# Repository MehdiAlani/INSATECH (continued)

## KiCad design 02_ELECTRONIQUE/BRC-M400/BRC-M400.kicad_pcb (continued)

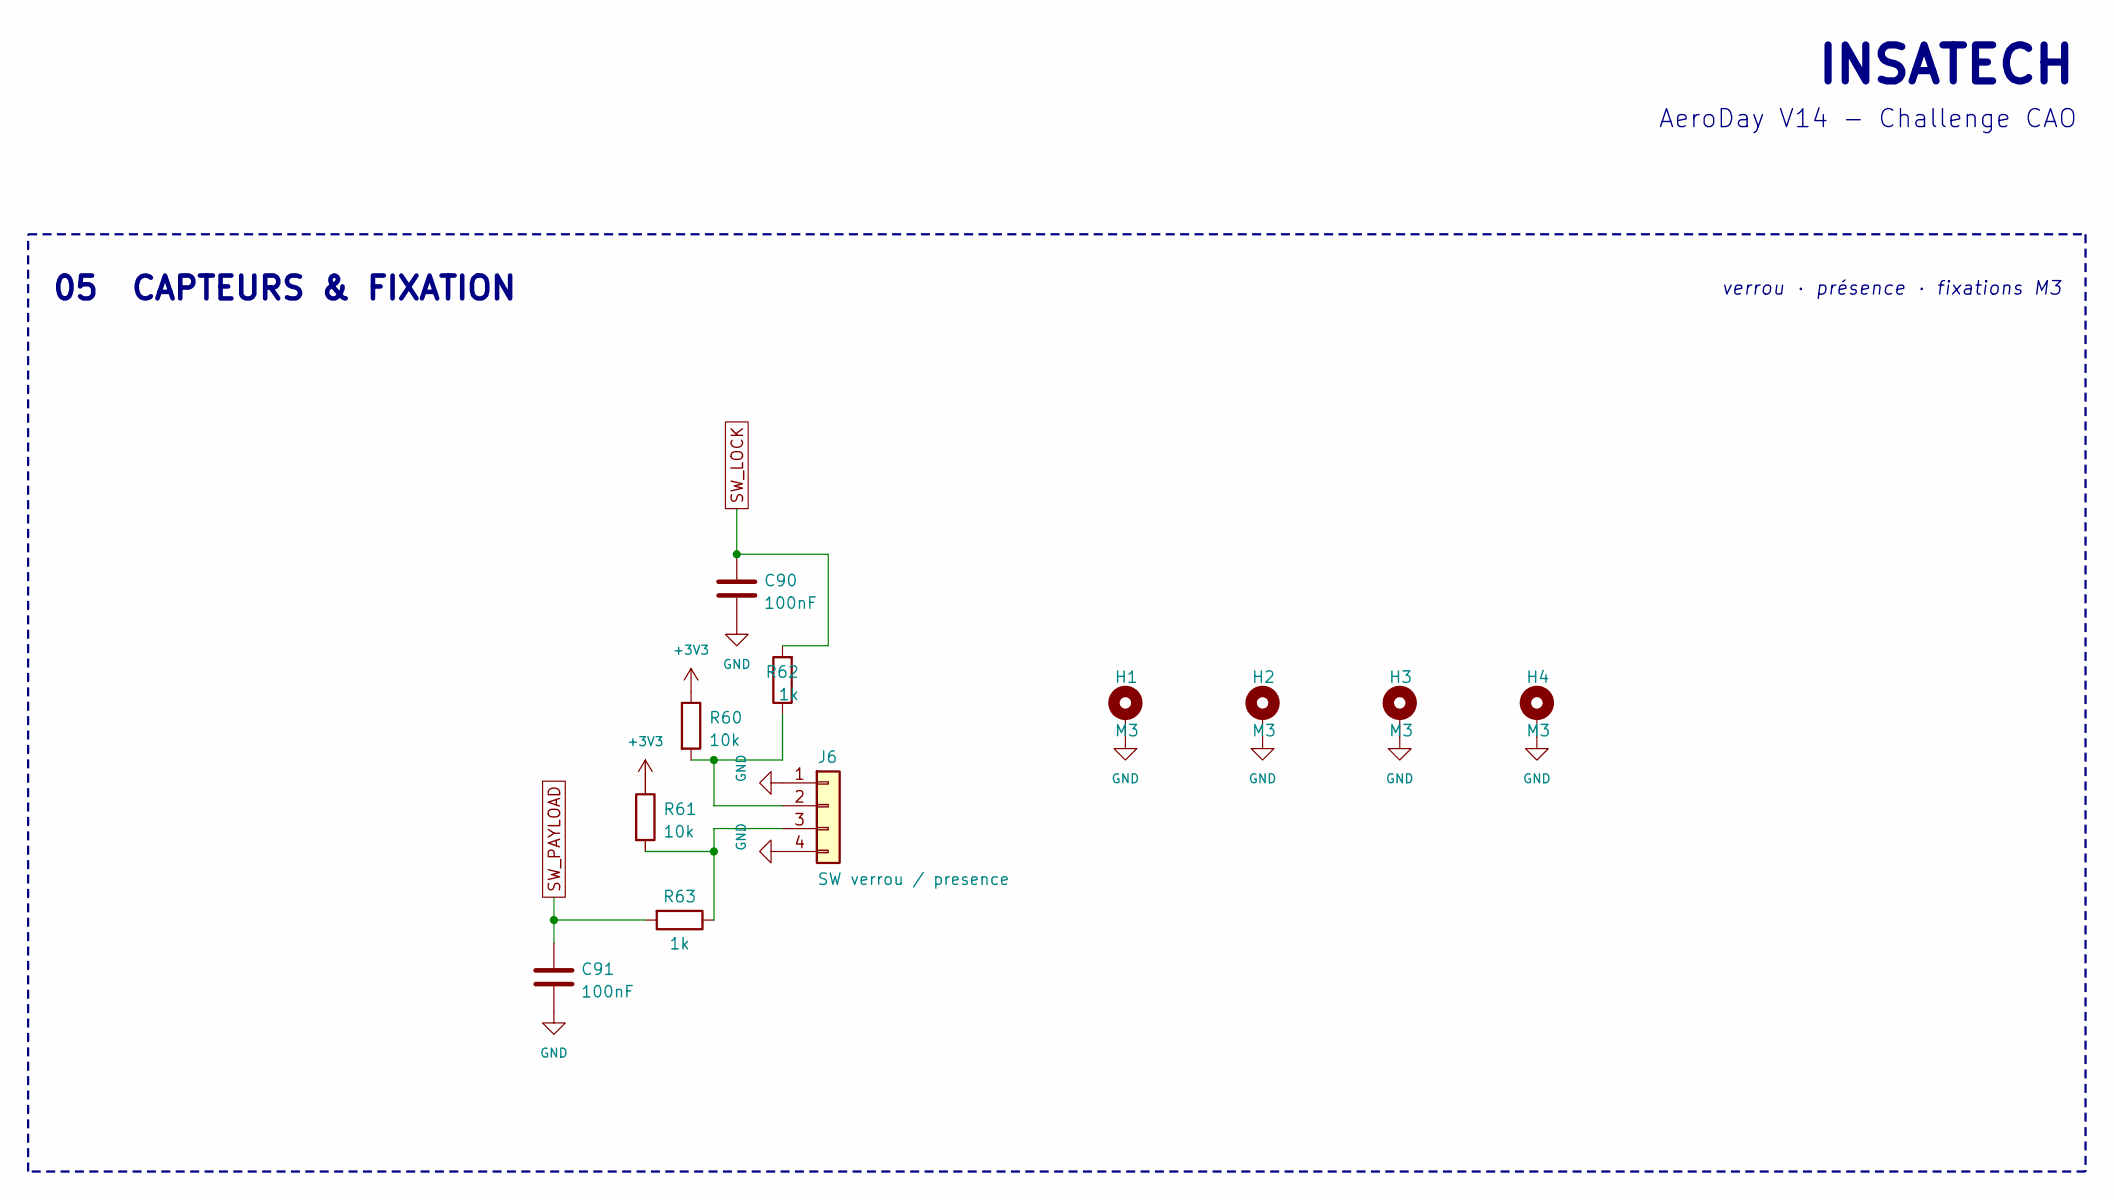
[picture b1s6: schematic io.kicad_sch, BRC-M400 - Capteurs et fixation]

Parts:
C90, C91: 100nF; C_0603_1608Metric
H1, H2, H3, H4: M3; MountingHole_3.2mm_M3_Pad_Via
J6: SW verrou / presence; JST_GH_SM04B-GHS-TB_1x04-1MP_P1.25mm_Horizontal; MPN SM04B-GHS-TB
R60, R61: 10k; R_0603_1608Metric
R62, R63: 1k; R_0603_1608Metric

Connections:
unnamed: J6.2, R60.2, R62.1
unnamed: J6.3, R61.2, R63.1
SW_LOCK: C90.1, R62.2; also elsewhere on the board
SW_PAYLOAD: C91.1, R63.2; also elsewhere on the board

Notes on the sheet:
INSATECH
AeroDay V14 - Challenge CAO
05 CAPTEURS & FIXATION
verrou · présence · fixations M3

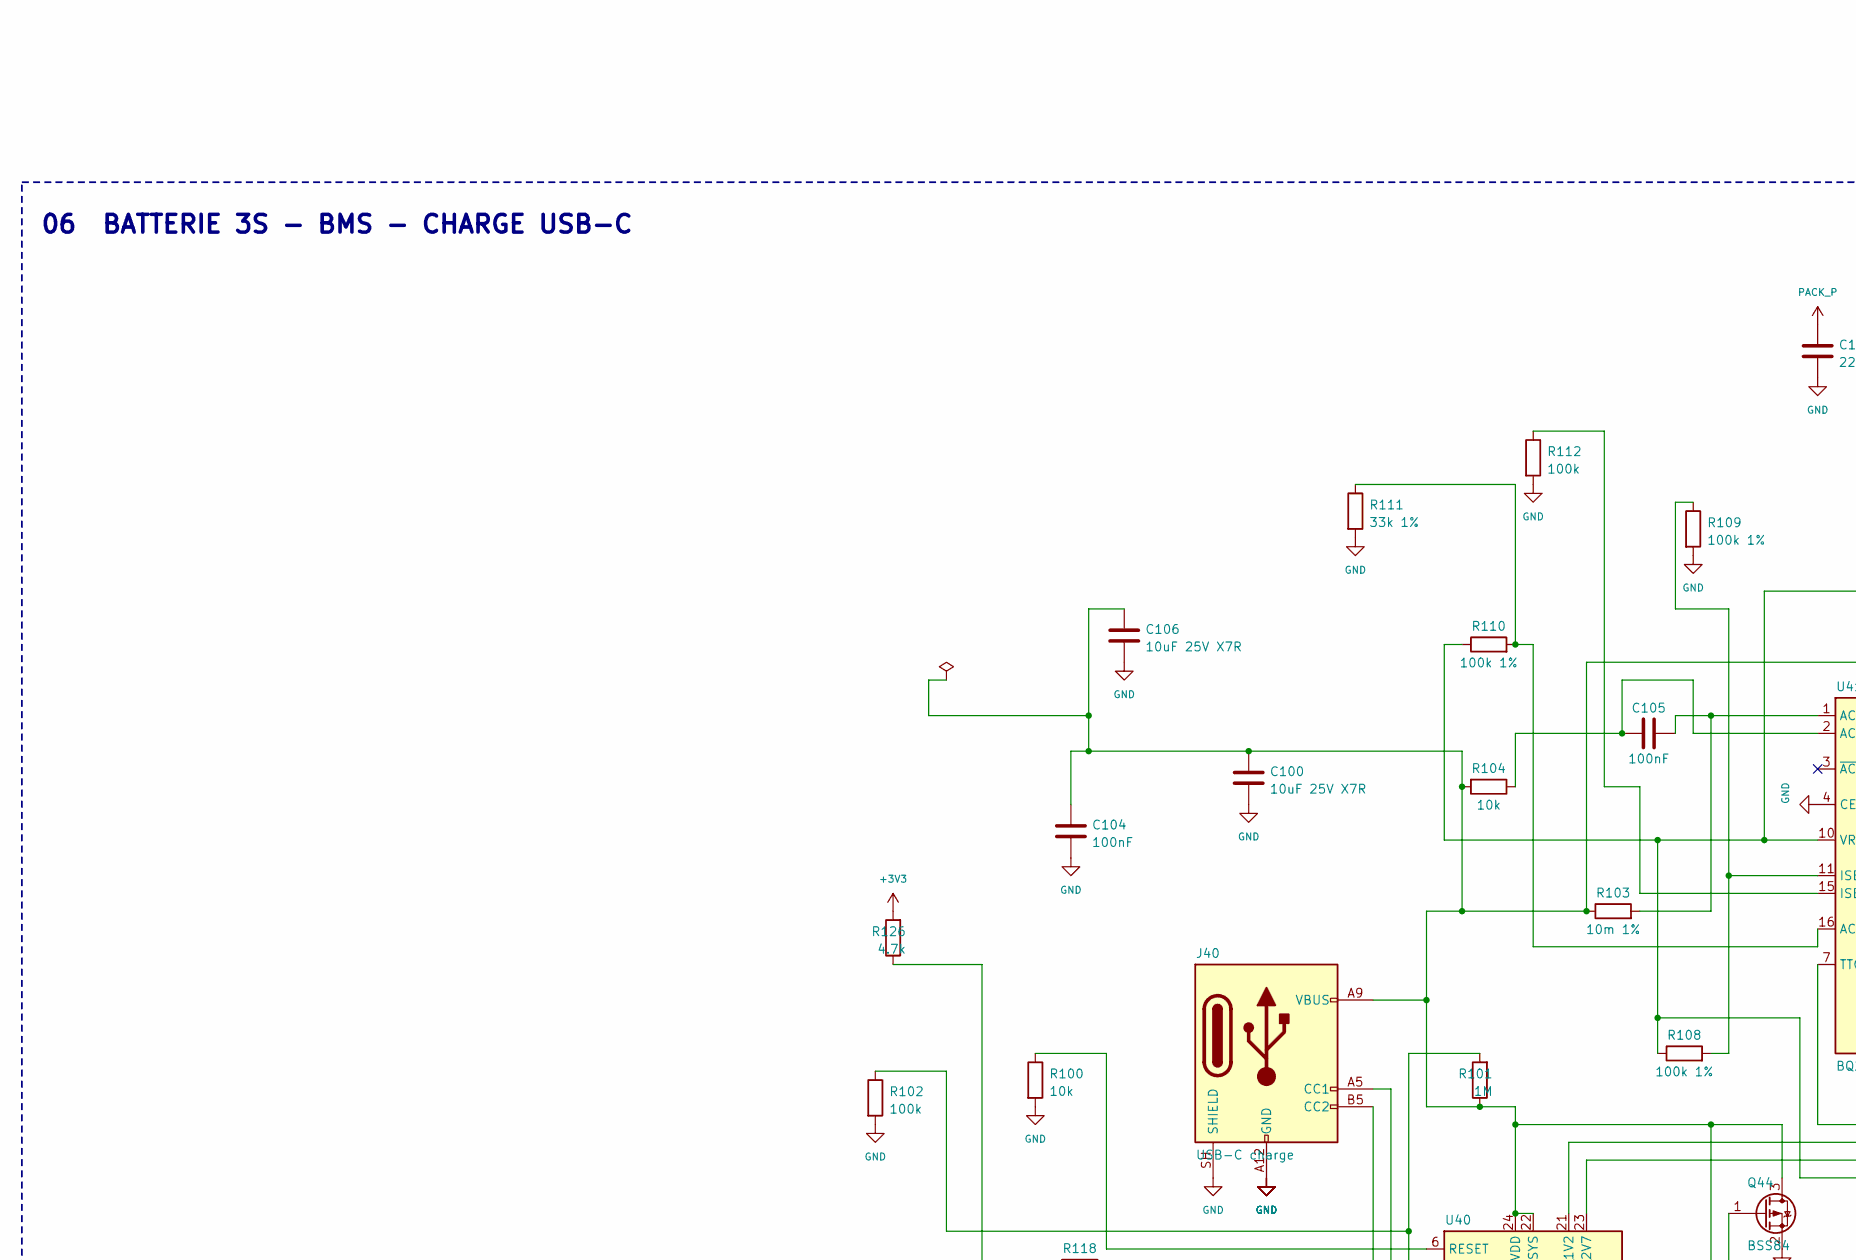
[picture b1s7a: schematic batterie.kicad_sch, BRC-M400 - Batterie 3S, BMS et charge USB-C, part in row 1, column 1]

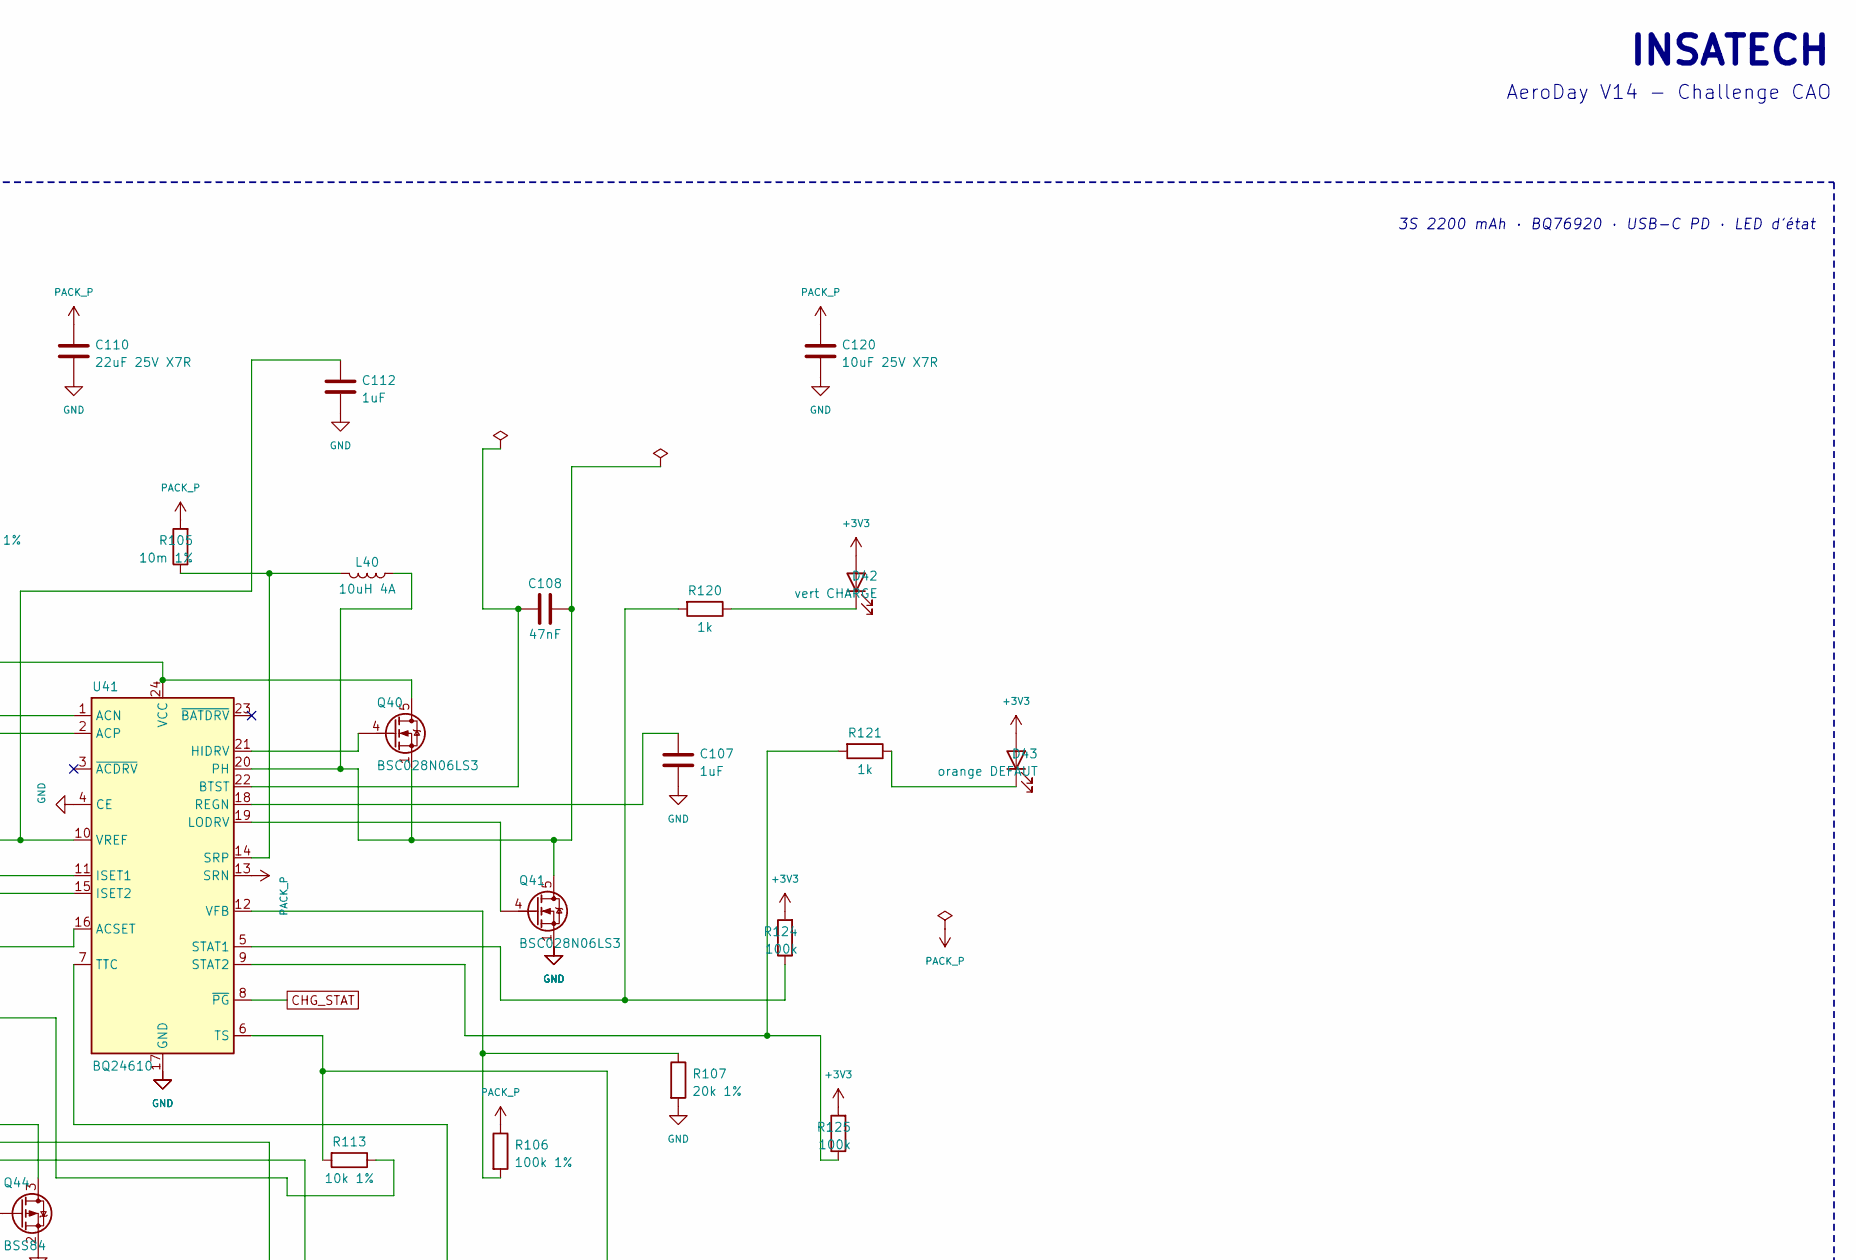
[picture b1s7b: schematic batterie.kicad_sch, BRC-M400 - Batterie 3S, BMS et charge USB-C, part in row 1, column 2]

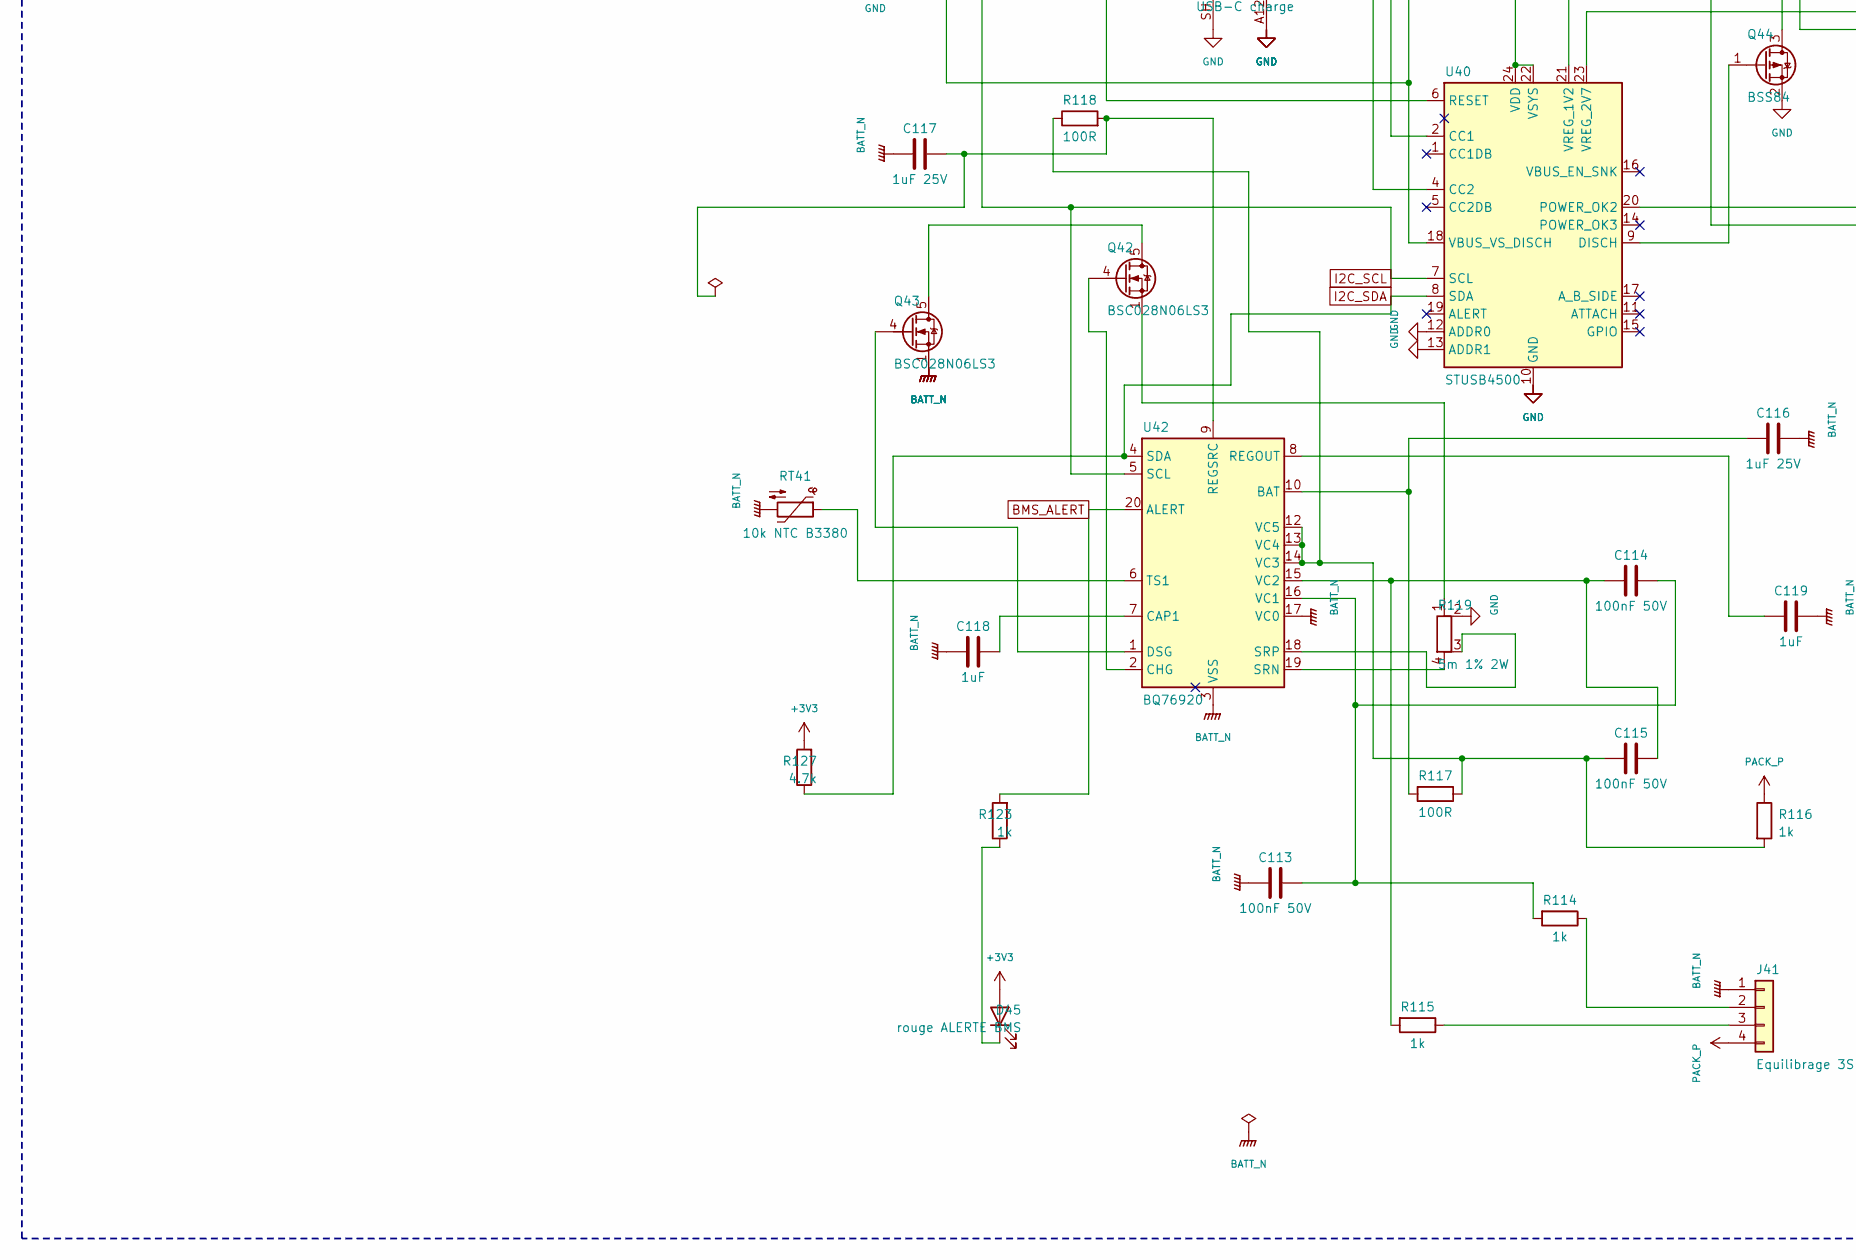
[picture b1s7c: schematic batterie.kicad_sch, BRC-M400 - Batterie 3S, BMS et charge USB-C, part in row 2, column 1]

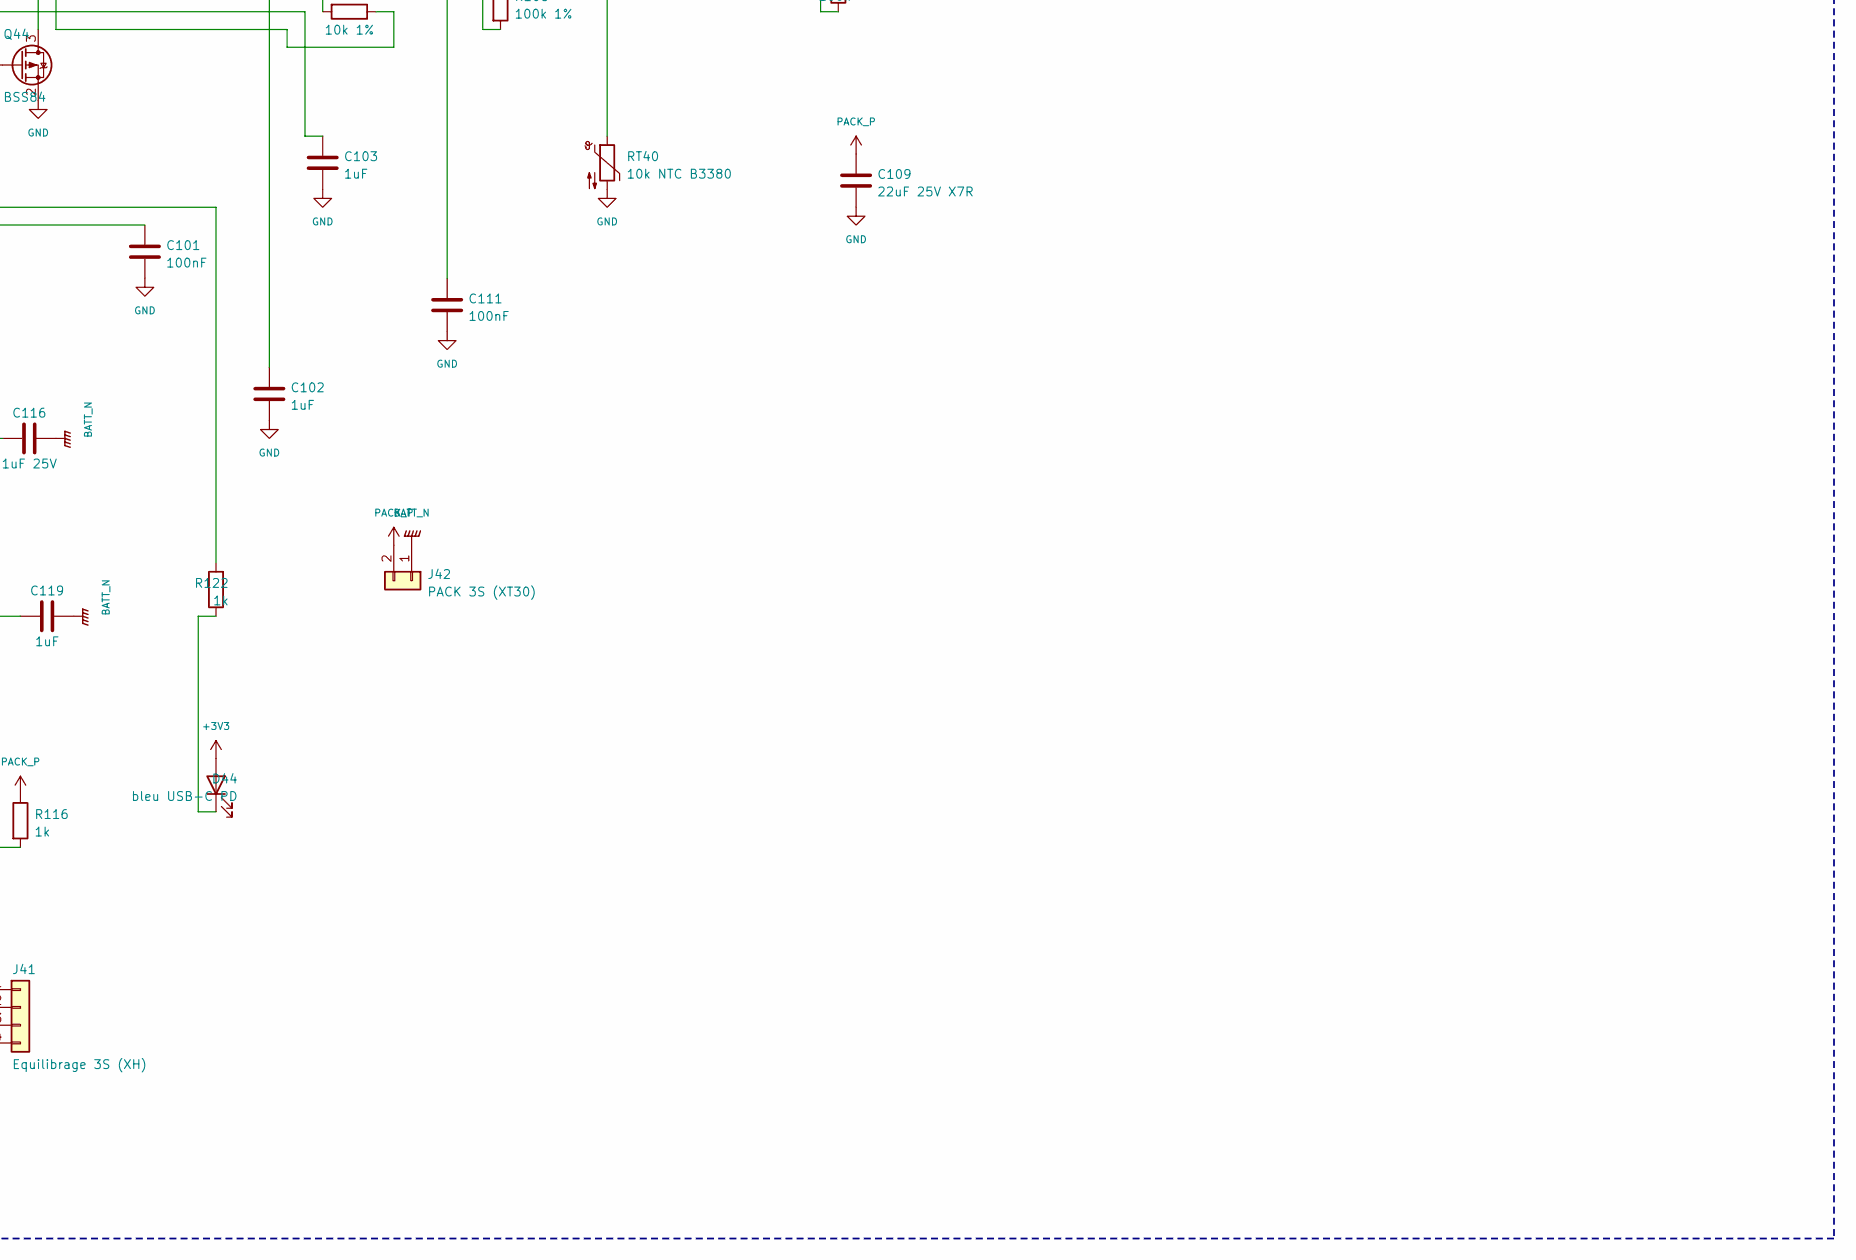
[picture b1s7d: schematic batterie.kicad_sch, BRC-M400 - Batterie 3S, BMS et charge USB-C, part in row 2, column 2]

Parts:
C100, C106, C120: 10uF 25V X7R; C_1210_3225Metric
C101: 100nF; C_0603_1608Metric
C102, C103, C112, C118, C119: 1uF; C_0402_1005Metric
C104, C105, C111: 100nF; C_0402_1005Metric
C107: 1uF; C_0603_1608Metric
C108: 47nF; C_0402_1005Metric
C109, C110: 22uF 25V X7R; C_1210_3225Metric
C113, C114, C115: 100nF 50V; C_0603_1608Metric
C116, C117: 1uF 25V; C_0603_1608Metric
D42: vert CHARGE; LED_0805_2012Metric
D43: orange DEFAUT; LED_0805_2012Metric
D44: bleu USB-C PD; LED_0805_2012Metric
D45: rouge ALERTE BMS; LED_0805_2012Metric
J40: USB-C charge; USB_C_Receptacle_GCT_USB4085; MPN USB4085-GF-A
J41: Equilibrage 3S (XH); JST_XH_B4B-XH-A_1x04_P2.50mm_Vertical; MPN B4B-XH-A
J42: PACK 3S (XT30); AMASS_XT30PW-M_1x02_P2.50mm_Horizontal; MPN XT30PW-M
L40: 10uH 4A; L_Bourns_SRN6045TA; MPN SRN6045TA-100M
Q40, Q41, Q42, Q43: BSC028N06LS3; TDSON-8-1; MPN BSC028N06LS3GATMA1
Q44: BSS84; SOT-23
R100, R104: 10k; R_0402_1005Metric
R101: 1M; R_0402_1005Metric
R102, R124, R125: 100k; R_0402_1005Metric
R103, R105: 10m 1%; R_2512_6332Metric; MPN CSS2512
R106, R108, R109, R110: 100k 1%; R_0603_1608Metric
R107: 20k 1%; R_0603_1608Metric
R111: 33k 1%; R_0603_1608Metric
R112: 100k; R_0603_1608Metric
R113: 10k 1%; R_0603_1608Metric
R114, R115, R116: 1k; R_0603_1608Metric
R117, R118: 100R; R_0603_1608Metric
R119: 5m 1% 2W; R_2512_6332Metric; MPN WSL2512R0050FEA
R120, R121, R122, R123: 1k; R_0402_1005Metric
R126, R127: 4.7k; R_0402_1005Metric
RT40, RT41: 10k NTC B3380; R_0603_1608Metric
U40: STUSB4500; QFN-24-1EP_4x4mm_P0.5mm_EP2.8x2.8mm; MPN STUSB4500QTR
U41: BQ24610; QFN-24-1EP_4x4mm_P0.5mm_EP2.5x2.5mm; MPN BQ24610RGER
U42: BQ76920; TSSOP-20_4.4x6.5mm_P0.65mm; MPN BQ76920PWR

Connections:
BATT_N: C113.2, C116.2, C117.2, C118.2, C119.2, J41.1, J42.1, Q43.1 (S), Q43.2 (S), Q43.3 (S), RT41.2, U42.3 (VSS), U42.17 (VC0)
BMS_ALERT: R123.2, U42.20 (ALERT); also elsewhere on the board
CHG_STAT: U41.8 (~PG); also elsewhere on the board
I2C_SCL: R126.1, U40.7 (SCL), U42.5 (SCL); also elsewhere on the board
I2C_SDA: R127.1, U40.8 (SDA), U42.4 (SDA); also elsewhere on the board
unnamed: D42.1 (K), R120.1
unnamed: D43.1 (K), R121.1
unnamed: D44.1 (K), R122.1
unnamed: D45.1 (K), R123.1
unnamed: J40.A5 (CC1), U40.2 (CC1)
unnamed: J40.B5 (CC2), U40.4 (CC2)
unnamed: J41.2, R114.1
unnamed: J41.3, R115.1
unnamed: C100.1, C101.1, C104.1, C106.1, J40.A4 (VBUS), J40.A9 (VBUS), J40.B4 (VBUS), J40.B9 (VBUS), Q40.5 (D), Q44.3 (D), R101.1, R103.1, R104.2, U40.22 (VSYS), U40.24 (VDD), U41.24 (VCC)
unnamed: Q40.4 (G), U41.21 (HIDRV)
unnamed: C108.2, L40.1, Q40.1 (S), Q40.2 (S), Q40.3 (S), Q41.5 (D), U41.20 (PH)
unnamed: Q41.4 (G), U41.19 (LODRV)
unnamed: Q42.5 (D), Q43.5 (D)
unnamed: Q42.4 (G), U42.2 (CHG)
unnamed: Q42.1 (S), Q42.2 (S), Q42.3 (S), R119.1
unnamed: Q43.4 (G), U42.1 (DSG)
unnamed: Q44.1 (G), U40.9 (DISCH)
unnamed: R122.2, U40.20 (POWER_OK2)
unnamed: R100.1, U40.6 (RESET)
unnamed: R101.2, R102.1, U40.18 (VBUS_VS_DISCH)
unnamed: C102.1, U40.21 (VREG_1V2)
unnamed: C103.1, U40.23 (VREG_2V7)
unnamed: C105.1, R103.2, U41.1 (ACN)
unnamed: C105.2, R104.1, U41.2 (ACP)
unnamed: R110.2, R111.1, U41.16 (ACSET)
unnamed: C108.1, U41.22 (BTST)
unnamed: R108.2, R109.1, U41.11 (ISET1)
unnamed: R112.1, U41.15 (ISET2)
unnamed: C107.1, U41.18 (REGN)
unnamed: L40.2, R105.1, U41.14 (SRP)
unnamed: R120.2, R124.1, U41.5 (STAT1)
unnamed: R121.2, R125.1, U41.9 (STAT2)
unnamed: R113.2, RT40.1, U41.6 (TS)
unnamed: C111.1, U41.7 (TTC)
unnamed: R106.2, R107.1, U41.12 (VFB)
unnamed: C112.1, R108.1, R110.1, R113.1, U41.10 (VREF)
unnamed: C116.1, R117.2, U42.10 (BAT)
unnamed: C118.1, U42.7 (CAP1)
unnamed: C119.1, U42.8 (REGOUT)
unnamed: C117.1, R118.2, U42.9 (REGSRC)
unnamed: R119.4, U42.19 (SRN)
unnamed: R119.3, U42.18 (SRP)
unnamed: RT41.1, U42.6 (TS1)
unnamed: C113.1, C114.2, R114.2, U42.16 (VC1)
unnamed: C114.1, C115.2, R115.2, U42.15 (VC2)
unnamed: C115.1, R116.2, R117.1, R118.1, U42.12 (VC5), U42.13 (VC4), U42.14 (VC3)
PACK_P: C109.1, C110.1, C120.1, J41.4, J42.2, R105.2, R106.1, R116.1, U41.13 (SRN); also elsewhere on the board

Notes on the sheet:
INSATECH
AeroDay V14 - Challenge CAO
06 BATTERIE 3S - BMS - CHARGE USB-C
3S 2200 mAh · BQ76920 · USB-C PD · LED d'état

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
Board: 4 copper layers, 226 parts (0 on the bottom side), 149 nets, no tracks yet.

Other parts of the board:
D2: MBR0540; D_SOD-123
L1: 10uH; L_0805_2012Metric

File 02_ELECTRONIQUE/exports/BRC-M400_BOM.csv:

"Repere","Valeur","Empreinte","MPN","Qte","DNP"
"C1,C2,C12","100nF 50V","Capacitor_SMD:C_0603_1608Metric","","3",""
"C3","470uF 35V low-ESR","Capacitor_THT:CP_Radial_D10.0mm_P5.00mm","","1",""
"C4","1uF 50V X7R","Capacitor_SMD:C_0805_2012Metric","","1",""
"C5,C82,C85,C93","10nF","Capacitor_SMD:C_0603_1608Metric","","4",""
"C6,C7","10uF 25V X7R","Capacitor_SMD:C_1210_3225Metric","","2",""
"C11,C81","10uF 50V X7R","Capacitor_SMD:C_1210_3225Metric","","2",""
"C13,C17,C19,C20,C84,C88,C90,C91,C92","100nF","Capacitor_SMD:C_0603_1608Metric","","9",""
"C14,C15","22uF 10V X5R","Capacitor_SMD:C_1210_3225Metric","","2",""
"C16","10uF 10V","Capacitor_SMD:C_0805_2012Metric","","1",""
"C30,C31,C32,C33,C37,C50,C51,C52,C55","100nF","Capacitor_SMD:C_0402_1005Metric","","9",""
"C34,C36","4.7uF","Capacitor_SMD:C_0603_1608Metric","","2",""
"C35","1uF","Capacitor_SMD:C_0402_1005Metric","","1",""
"C38,C39,C56","10pF C0G","Capacitor_SMD:C_0402_1005Metric","","3",""
"C53","10uF","Capacitor_SMD:C_0805_2012Metric","","1",""
"C54","470nF","Capacitor_SMD:C_0402_1005Metric","","1",""
"C57","47pF","Capacitor_SMD:C_0402_1005Metric","","1",""
"C58,C67,C68","1nF","Capacitor_SMD:C_0402_1005Metric","","3",""
"C59,C60,C61,C62,C63,C64,C65,C66","TUNE","Capacitor_SMD:C_0402_1005Metric","","8",""
"C69","47pF C0G","Capacitor_SMD:C_0402_1005Metric","","1",""
"C80","100uF 35V","Capacitor_SMD:CP_Elec_8x10","","1",""
"C83,C86,C87,C89","1uF 25V","Capacitor_SMD:C_0603_1608Metric","","4",""
"D1","SMAJ26A","Diode_SMD:D_SMA","SMAJ26A","1",""
"D10","LED RGB","LED_SMD:LED_RGB_1210","","1",""
"D30","SS54","Diode_SMD:D_SMC","SS54","1",""
"D31,D32,D34","SS34","Diode_SMD:D_SMA","SS34","3",""
"D33,D35","SMAJ20A","Diode_SMD:D_SMA","SMAJ20A","2",""
"F1","5A 32V fast","Fuse:Fuse_1206_3216Metric","0466005.NR","1",""
"FB1","600R@100MHz","Inductor_SMD:L_0603_1608Metric","BLM18PG600SN1D","1",""
"FB20","600R@100MHz","Inductor_SMD:L_0402_1005Metric","","1",""
"J1","E-Port V2 VCC (XT30)","Connector_AMASS:AMASS_XT30PW-M_1x02_P2.50mm_Horizontal","XT30PW-M","1",""
"J2","DJI PSDK UART","Connector_JST:JST_GH_SM04B-GHS-TB_1x04-1MP_P1.25mm_Horizontal","SM04B-GHS-TB","1",""
"J6","SW verrou / presence","Connector_JST:JST_GH_SM04B-GHS-TB_1x04-1MP_P1.25mm_Horizontal","SM04B-GHS-TB","1",""
"J7","SWD Cortex-10","Connector_PinHeader_1.27mm:PinHeader_2x05_P1.27mm_Vertical","","1",""
"J20","SMA 868MHz","Connector_Coaxial:SMA_Amphenol_132289_EdgeMount","132289","1",""
"J31","LED ARRAY (XT30)","Connector_AMASS:AMASS_XT30PW-F_1x02_P2.50mm_Horizontal","XT30PW-F","1",""
"J32","SIRENE (XT30)","Connector_AMASS:AMASS_XT30PW-F_1x02_P2.50mm_Horizontal","XT30PW-F","1",""
"J33","MAINTIEN (XT30)","Connector_AMASS:AMASS_XT30PW-F_1x02_P2.50mm_Horizontal","XT30PW-F","1",""
"J34","EJECTION (XT30)","Connector_AMASS:AMASS_XT30PW-F_1x02_P2.50mm_Horizontal","XT30PW-F","1",""
"L2","15uH 2.5A","Inductor_SMD:L_Bourns_SRN6045TA","SRN6045TA-150M","1",""
"L20","15uH 150mA","Inductor_SMD:L_0805_2012Metric","","1",""
"L21,L22,L23,L24,L25","TUNE","Inductor_SMD:L_0402_1005Metric","","5",""
"Q1,Q32,Q33,Q34,Q35","BSC028N06LS3","Package_TO_SOT_SMD:TDSON-8-1","BSC028N06LS3GATMA1","5",""
"Q30","SUD50P06-15","Package_TO_SOT_SMD:TO-252-2","SUD50P06-15-GE3","1",""
"Q31","MMBT3904","Package_TO_SOT_SMD:SOT-23","","1",""
"R1","91k 1%","Resistor_SMD:R_0603_1608Metric","","1",""
"R2,R8","10k 1%","Resistor_SMD:R_0603_1608Metric","","2",""
"R4,R35,R38,R42,R46,R51","100k","Resistor_SMD:R_0603_1608Metric","","6",""
"R5,R7","100k 1%","Resistor_SMD:R_0603_1608Metric","","2",""
"R6","22.1k 1%","Resistor_SMD:R_0603_1608Metric","","1",""
"R10","10k","Resistor_SMD:R_0402_1005Metric","","1",""
"R11,R12,R13","1k","Resistor_SMD:R_0402_1005Metric","","3",""
"R14,R15,R21,R22","100R","Resistor_SMD:R_0402_1005Metric","","4",""
"R20","220R","Resistor_SMD:R_0402_1005Metric","","1",""
"R23","0R","Resistor_SMD:R_0402_1005Metric","","1",""
"R30,R33,R34,R39,R45,R49,R54,R60,R61","10k","Resistor_SMD:R_0603_1608Metric","","9",""
"R31,R43,R47,R52","4.7R","Resistor_SMD:R_0603_1608Metric","","4",""
"R32,R44,R48,R53","1R","Resistor_SMD:R_0603_1608Metric","","4",""
"R36,R37,R41,R62,R63","1k","Resistor_SMD:R_0603_1608Metric","","5",""
"R40,R50,R55","10mR 1W 1%","Resistor_SMD:R_2512_6332Metric","","3",""
"U1","LM74700-Q1","Package_TO_SOT_SMD:SOT-23-6","LM74700QDBVRQ1","1",""
"U2","TPS7A4101","Package_SO:Texas_DGN0008B_VSSOP-8-1EP_3x3mm_P0.65mm_EP2x3mm_Mask1.88x1.98mm_ThermalVias","TPS7A4101DGNR","1",""
"U3","LMR51430","Package_TO_SOT_SMD:SOT-23-6","LMR51430XDDCR","1",""
"U4","TPS3808G33","Package_TO_SOT_SMD:SOT-23-6","TPS3808G33DBVR","1",""
"U10","STM32U585CIU6","Package_DFN_QFN:QFN-48-1EP_7x7mm_P0.5mm_EP5.6x5.6mm","STM32U585CIU6","1",""
"U20","SX1262IMLTRT","Package_DFN_QFN:QFN-24-1EP_4x4mm_P0.5mm_EP2.6x2.6mm","SX1262IMLTRT","1",""
"U21","AS179-92LF","Package_TO_SOT_SMD:SOT-363_SC-70-6","AS179-92LF","1",""
"U30,U32,U36","INA181A2 G=50","Package_TO_SOT_SMD:SOT-23-6","INA181A2IDBVR","3",""
"U31,U33,U34,U35","UCC27511A","Package_TO_SOT_SMD:SOT-23-6","UCC27511ADBVR","4",""
"X1","32.768kHz CL7pF","Crystal:Crystal_SMD_3215-2Pin_3.2x1.5mm","ABS07-120-32.768KHZ-T","1",""
"Y20","TCXO 32MHz 1.8V","Oscillator:Oscillator_SMD_Kyocera_2520-6Pin_2.5x2.0mm","","1",""

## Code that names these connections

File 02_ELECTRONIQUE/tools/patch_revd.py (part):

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# ---------------------------------------------------------------- MCU: drop PSDK, add I2C
sub('"PSDK : DJI fournit la lib precompilee armcc_cortex-m33 -> compilation Keil MDK (Arm Compiler 6).",\n',
    '"Module AUTONOME : aucune liaison avec le controleur de vol. L\'ordre de largage arrive par LoRa.",\n')
sub('"USART1 (PA9/PA10) 921600 bauds vers le kit E-Port V2 ; R14/R15 = protection du cable.",\n',
    '"I2C (PA9/PA10, instance a confirmer sous CubeMX) : BMS BQ76920 + STUSB4500 ; repli I2C logiciel possible.",\n')
sub('"ADC1 : PA0 VIN, PA1 I_HOLD, PA2 I_LED, PA3 I_EJECT. PWM : TIM1_CH1 maintien, TIM2_CH1 ejection, TIM15_CH1 LED. PB12 ARM.",',
    '"ADC1 : PA0 pack, PA1 I_HOLD, PA2 I_LED, PA3 I_EJECT. PWM : TIM1_CH1 maintien, TIM2_CH1 ejection, TIM15_CH1 LED. PB12 ARM.",')
sub('30: "PSDK_TX", 31: "PSDK_RX", 32: None, 33: None,',
    '30: "I2C_SCL", 31: "I2C_SDA", 32: "BMS_ALERT", 33: "CHG_STAT",')
sub('''    Part("J2", "Connector_Generic:Conn_01x04", "DJI PSDK UART", JST_GH4,
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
